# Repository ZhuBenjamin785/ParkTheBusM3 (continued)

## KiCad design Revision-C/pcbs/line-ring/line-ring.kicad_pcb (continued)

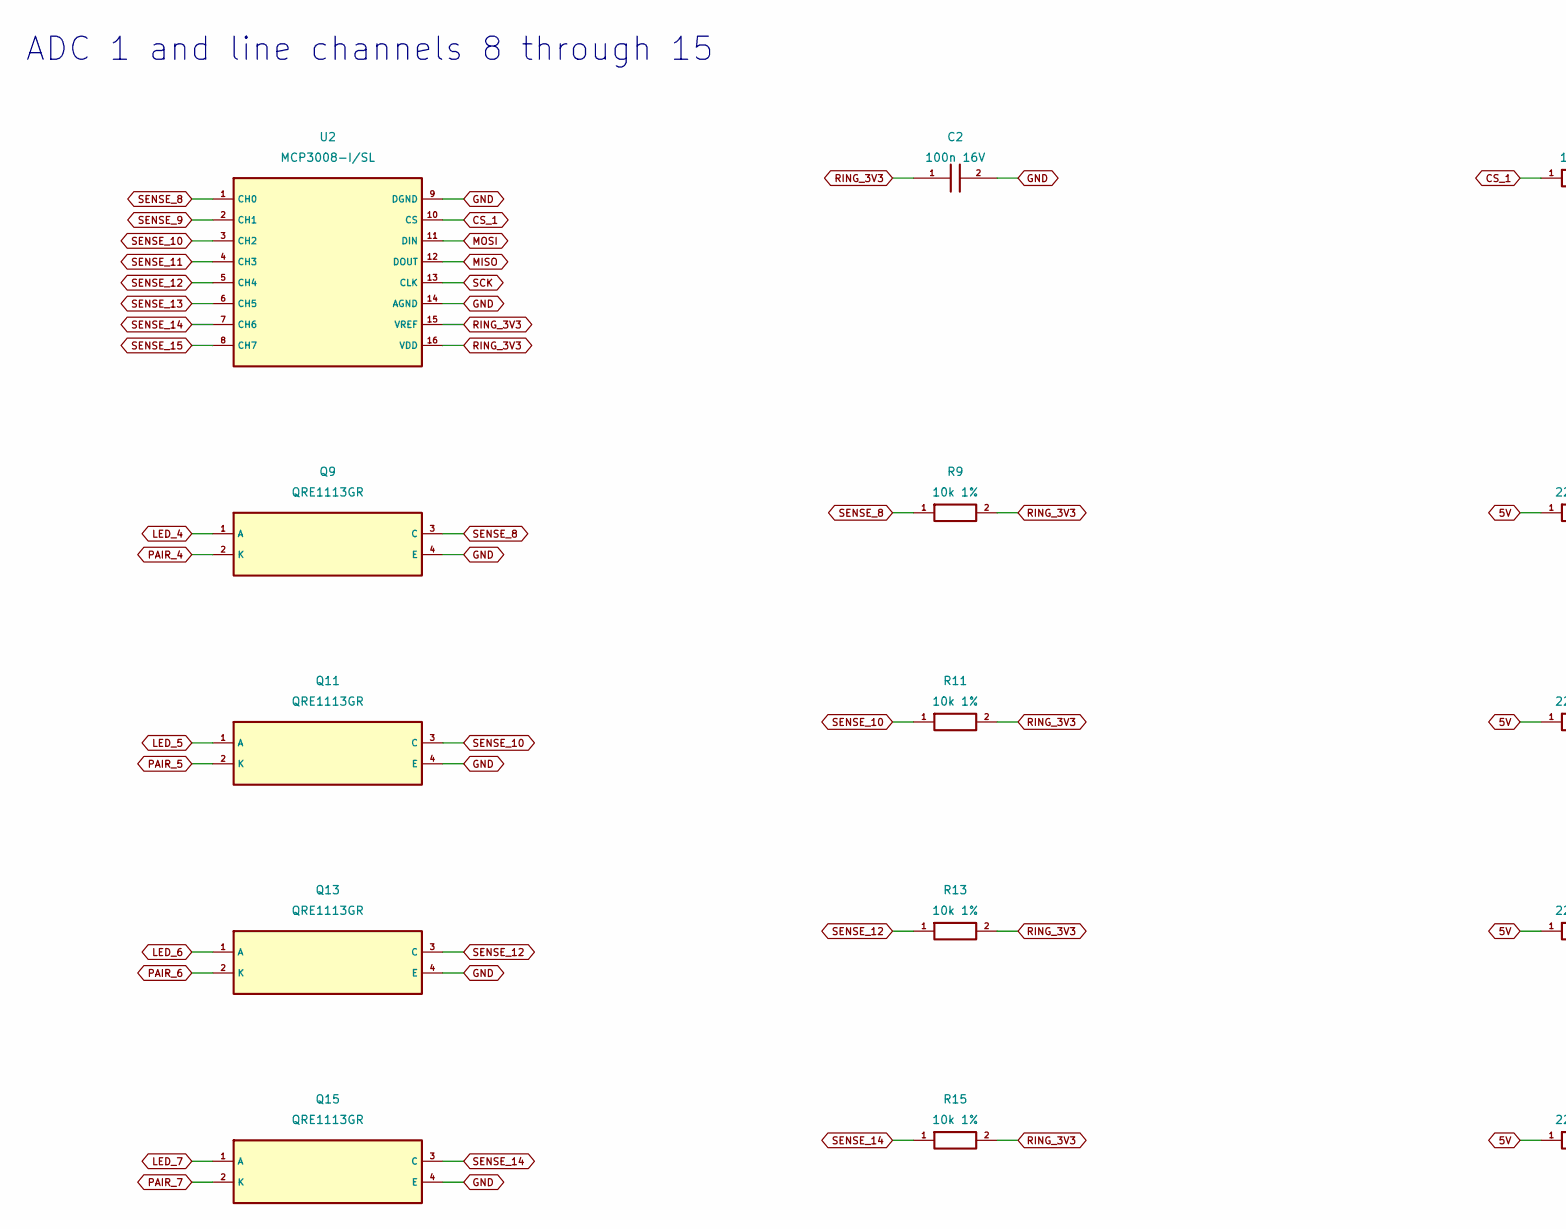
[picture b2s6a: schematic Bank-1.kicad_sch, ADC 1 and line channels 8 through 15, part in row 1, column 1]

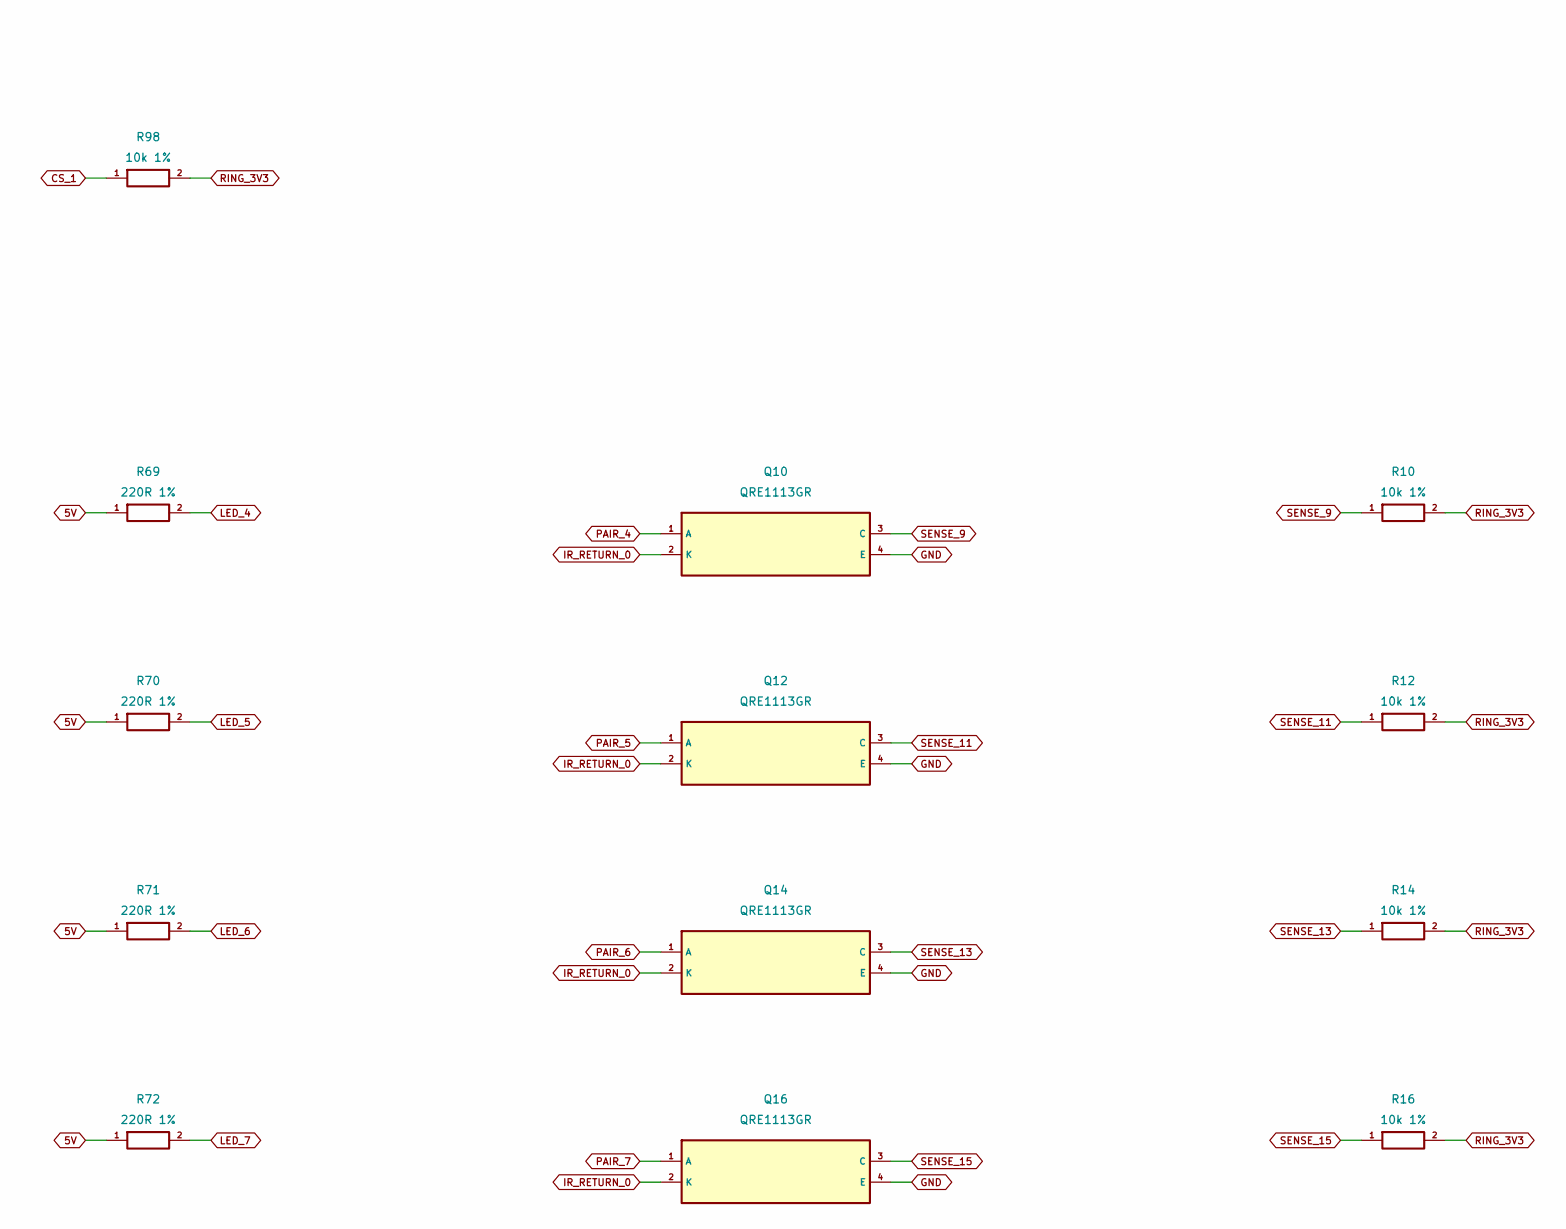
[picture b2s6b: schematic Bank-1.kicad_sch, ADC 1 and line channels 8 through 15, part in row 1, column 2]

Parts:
C2: 100n 16V; C_0805_2012Metric
Q9, Q10, Q11, Q12, Q13, Q14, Q15, Q16: QRE1113GR; OnSemi_CASE100CY
R9, R10, R11, R12, R13, R14, R15, R16, R98: 10k 1%; R_0805_2012Metric
R69, R70, R71, R72: 220R 1%; R_0805_2012Metric
U2: MCP3008-I/SL; SOIC-16_3.9x9.9mm_P1.27mm

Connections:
5V: R69.1, R70.1, R71.1, R72.1; also elsewhere on the board
CS_1: R98.1, U2.10 (CS); also elsewhere on the board
GND: C2.2, Q9.4 (E), Q10.4 (E), Q11.4 (E), Q12.4 (E), Q13.4 (E), Q14.4 (E), Q15.4 (E), Q16.4 (E), U2.9 (DGND), U2.14 (AGND); also elsewhere on the board
IR_RETURN_0: Q10.2 (K), Q12.2 (K), Q14.2 (K), Q16.2 (K); also elsewhere on the board
LED_4: Q9.1 (A), R69.2
LED_5: Q11.1 (A), R70.2
LED_6: Q13.1 (A), R71.2
LED_7: Q15.1 (A), R72.2
MISO: U2.12 (DOUT); also elsewhere on the board
MOSI: U2.11 (DIN); also elsewhere on the board
PAIR_4: Q9.2 (K), Q10.1 (A)
PAIR_5: Q11.2 (K), Q12.1 (A)
PAIR_6: Q13.2 (K), Q14.1 (A)
PAIR_7: Q15.2 (K), Q16.1 (A)
RING_3V3: C2.1, R9.2, R10.2, R11.2, R12.2, R13.2, R14.2, R15.2, R16.2, R98.2, U2.15 (VREF), U2.16 (VDD); also elsewhere on the board
SCK: U2.13 (CLK); also elsewhere on the board
SENSE_8: Q9.3 (C), R9.1, U2.1 (CH0)
SENSE_9: Q10.3 (C), R10.1, U2.2 (CH1)
SENSE_10: Q11.3 (C), R11.1, U2.3 (CH2)
SENSE_11: Q12.3 (C), R12.1, U2.4 (CH3)
SENSE_12: Q13.3 (C), R13.1, U2.5 (CH4)
SENSE_13: Q14.3 (C), R14.1, U2.6 (CH5)
SENSE_14: Q15.3 (C), R15.1, U2.7 (CH6)
SENSE_15: Q16.3 (C), R16.1, U2.8 (CH7)

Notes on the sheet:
ADC 1 and line channels 8 through 15

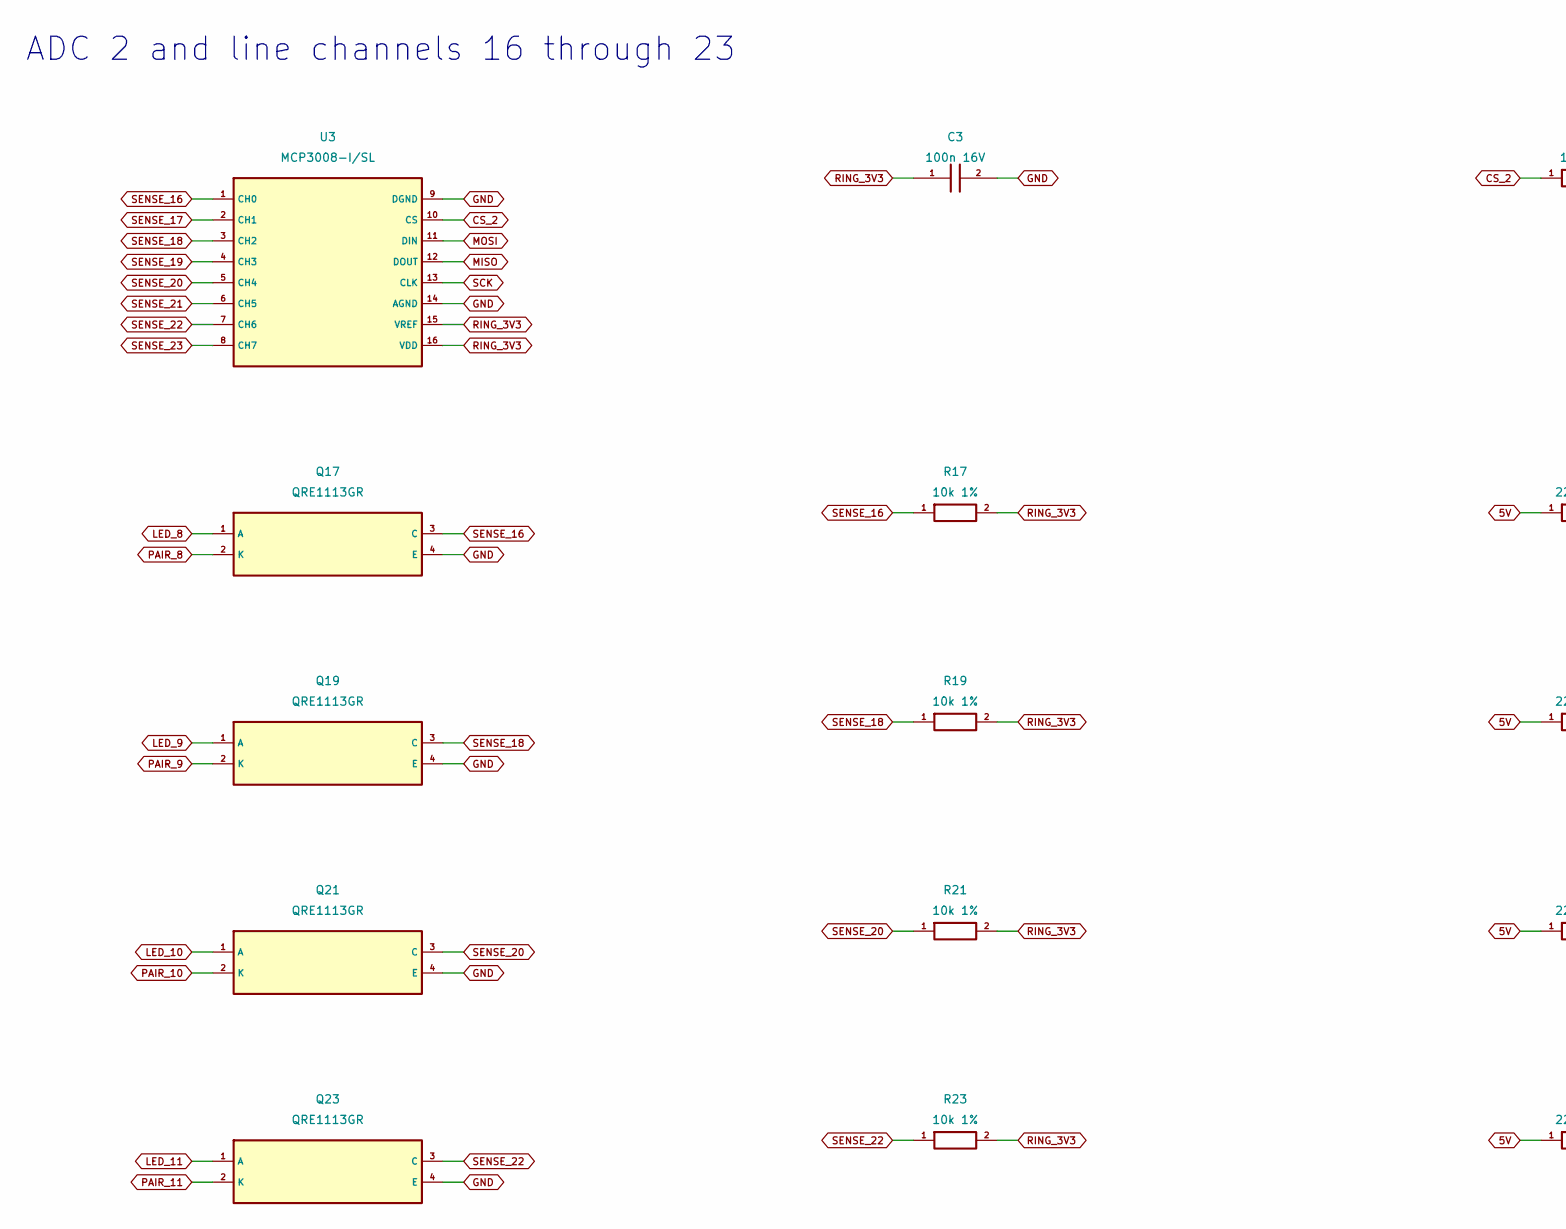
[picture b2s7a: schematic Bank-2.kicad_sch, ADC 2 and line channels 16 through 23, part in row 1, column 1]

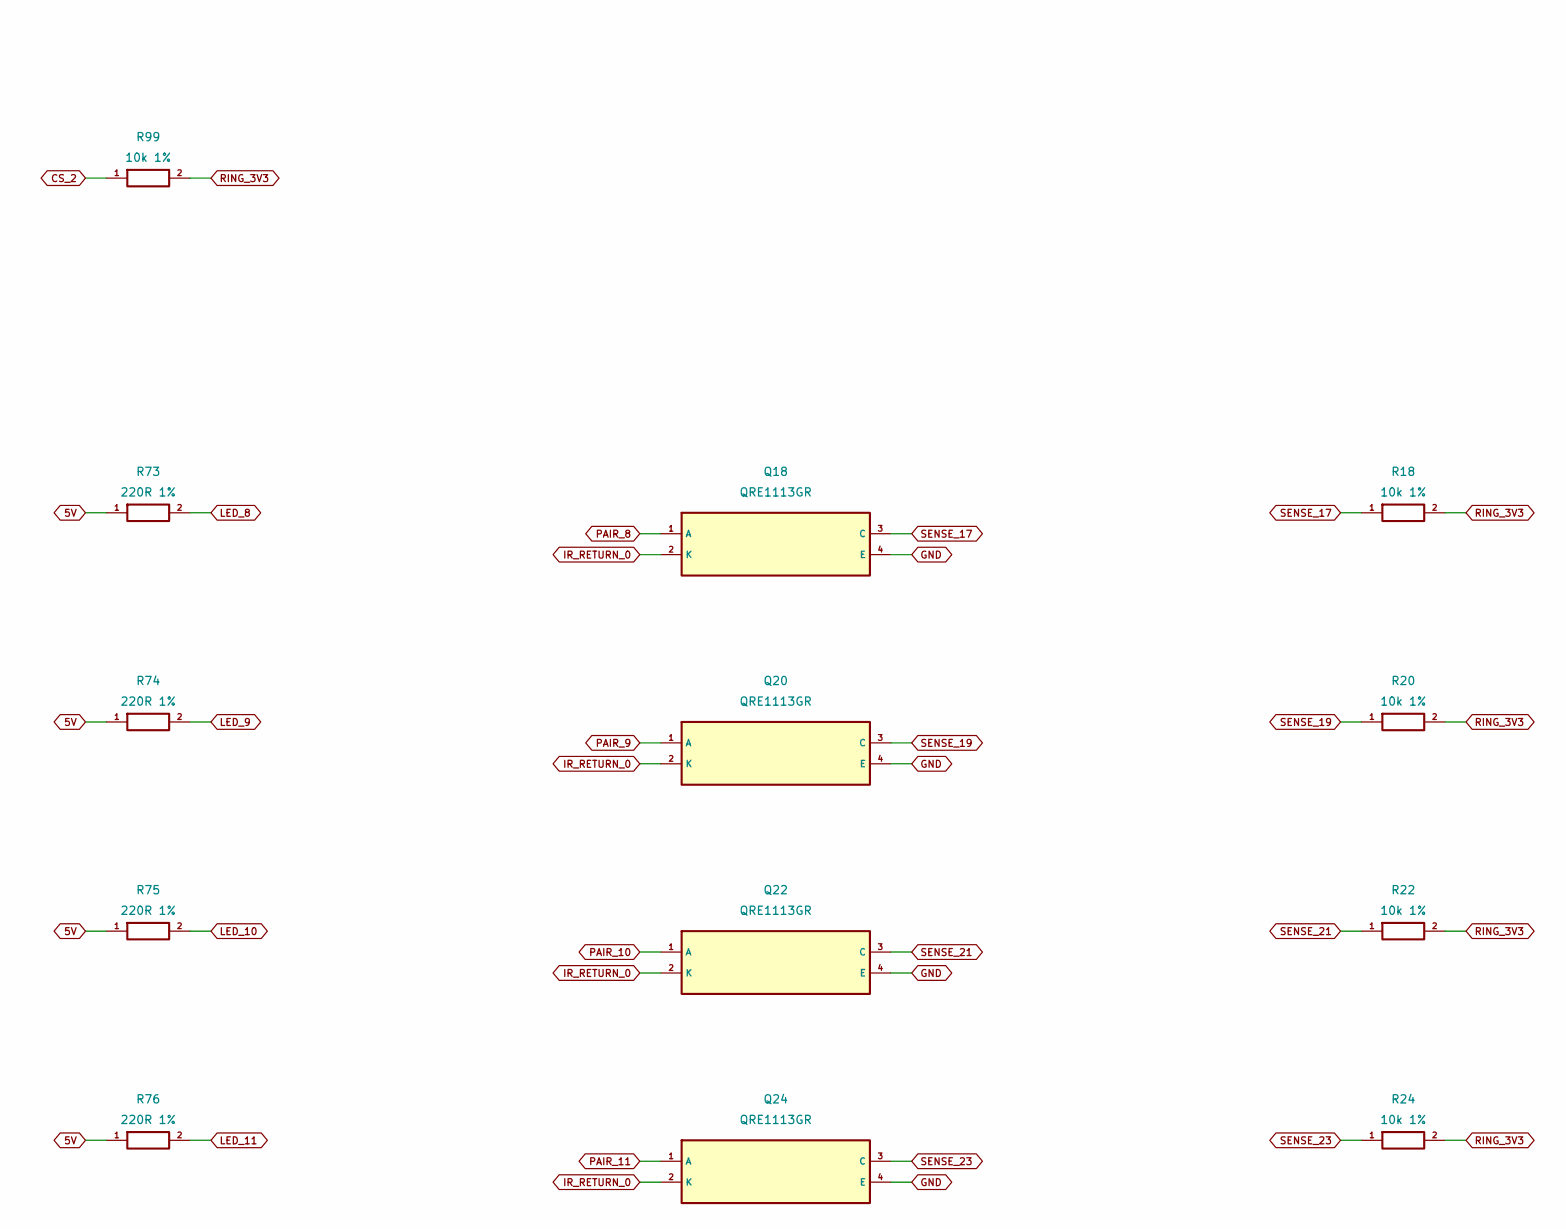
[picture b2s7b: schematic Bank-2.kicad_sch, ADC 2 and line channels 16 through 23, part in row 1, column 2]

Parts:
C3: 100n 16V; C_0805_2012Metric
Q17, Q18, Q19, Q20, Q21, Q22, Q23, Q24: QRE1113GR; OnSemi_CASE100CY
R17, R18, R19, R20, R21, R22, R23, R24, R99: 10k 1%; R_0805_2012Metric
R73, R74, R75, R76: 220R 1%; R_0805_2012Metric
U3: MCP3008-I/SL; SOIC-16_3.9x9.9mm_P1.27mm

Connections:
5V: R73.1, R74.1, R75.1, R76.1; also elsewhere on the board
CS_2: R99.1, U3.10 (CS); also elsewhere on the board
GND: C3.2, Q17.4 (E), Q18.4 (E), Q19.4 (E), Q20.4 (E), Q21.4 (E), Q22.4 (E), Q23.4 (E), Q24.4 (E), U3.9 (DGND), U3.14 (AGND); also elsewhere on the board
IR_RETURN_0: Q18.2 (K), Q20.2 (K), Q22.2 (K), Q24.2 (K); also elsewhere on the board
LED_8: Q17.1 (A), R73.2
LED_9: Q19.1 (A), R74.2
LED_10: Q21.1 (A), R75.2
LED_11: Q23.1 (A), R76.2
MISO: U3.12 (DOUT); also elsewhere on the board
MOSI: U3.11 (DIN); also elsewhere on the board
PAIR_8: Q17.2 (K), Q18.1 (A)
PAIR_9: Q19.2 (K), Q20.1 (A)
PAIR_10: Q21.2 (K), Q22.1 (A)
PAIR_11: Q23.2 (K), Q24.1 (A)
RING_3V3: C3.1, R17.2, R18.2, R19.2, R20.2, R21.2, R22.2, R23.2, R24.2, R99.2, U3.15 (VREF), U3.16 (VDD); also elsewhere on the board
SCK: U3.13 (CLK); also elsewhere on the board
SENSE_16: Q17.3 (C), R17.1, U3.1 (CH0)
SENSE_17: Q18.3 (C), R18.1, U3.2 (CH1)
SENSE_18: Q19.3 (C), R19.1, U3.3 (CH2)
SENSE_19: Q20.3 (C), R20.1, U3.4 (CH3)
SENSE_20: Q21.3 (C), R21.1, U3.5 (CH4)
SENSE_21: Q22.3 (C), R22.1, U3.6 (CH5)
SENSE_22: Q23.3 (C), R23.1, U3.7 (CH6)
SENSE_23: Q24.3 (C), R24.1, U3.8 (CH7)

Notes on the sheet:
ADC 2 and line channels 16 through 23

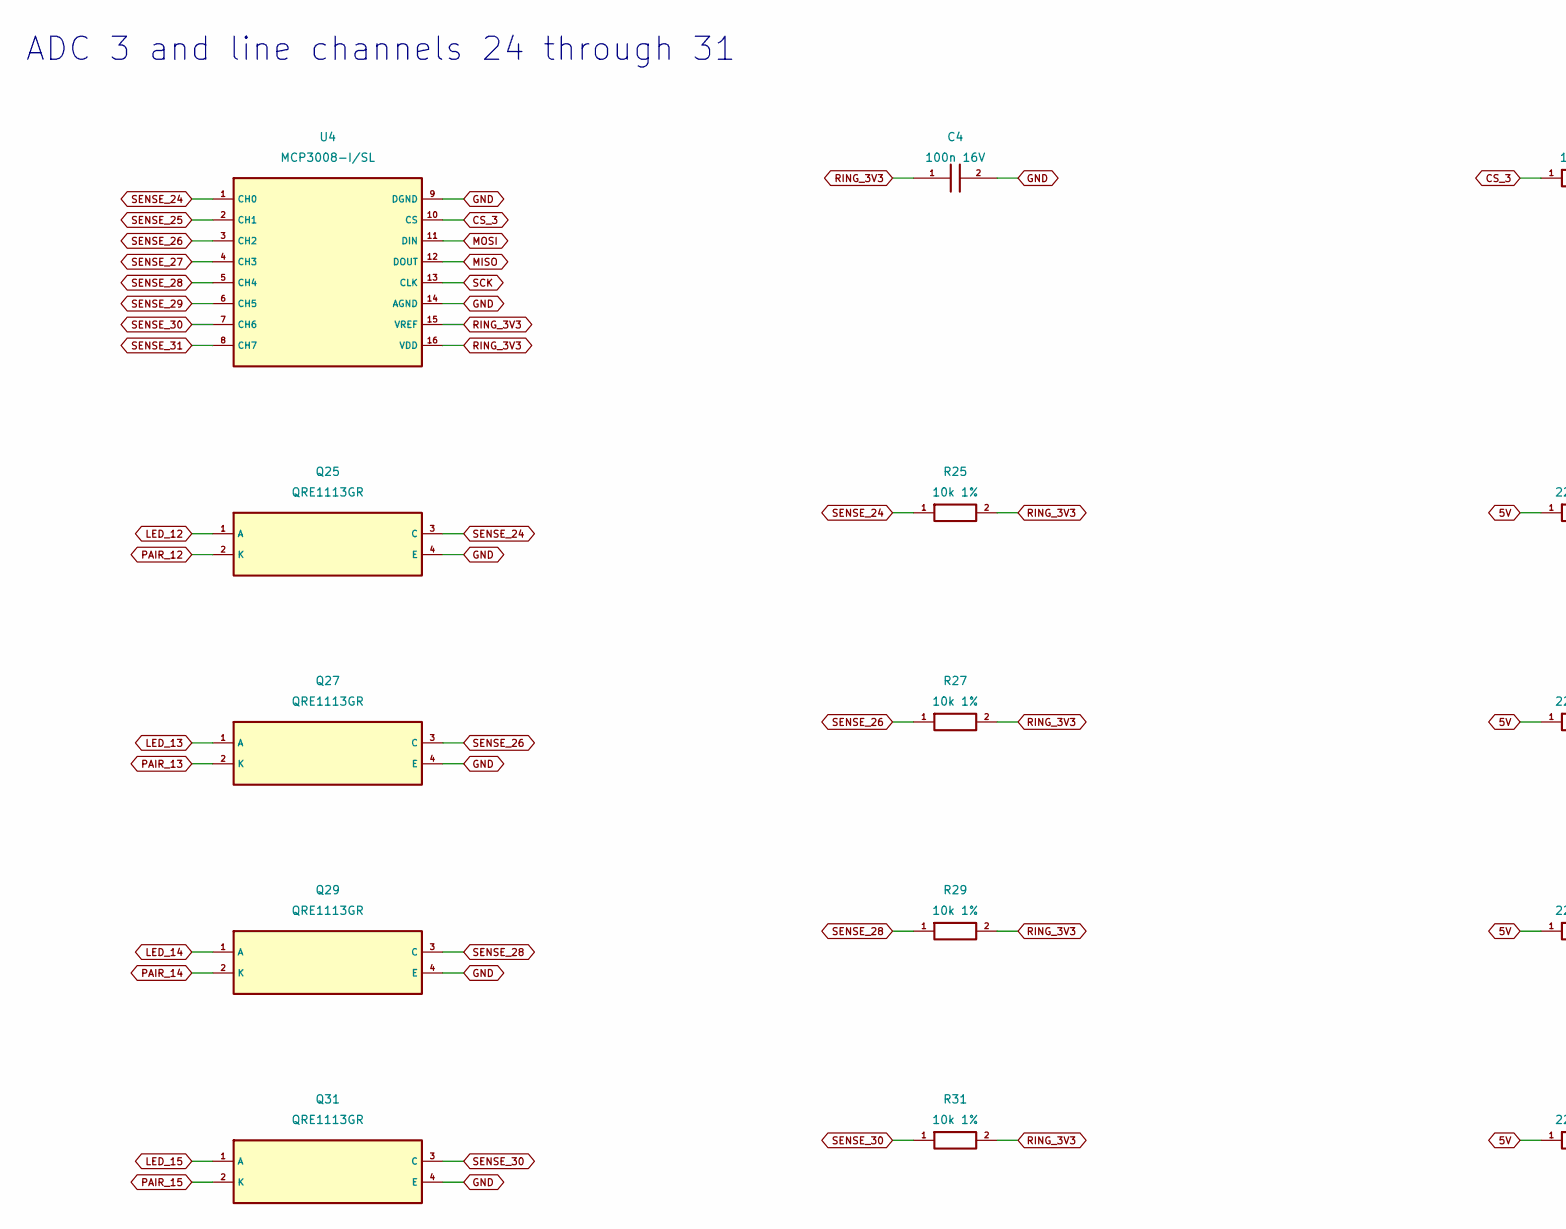
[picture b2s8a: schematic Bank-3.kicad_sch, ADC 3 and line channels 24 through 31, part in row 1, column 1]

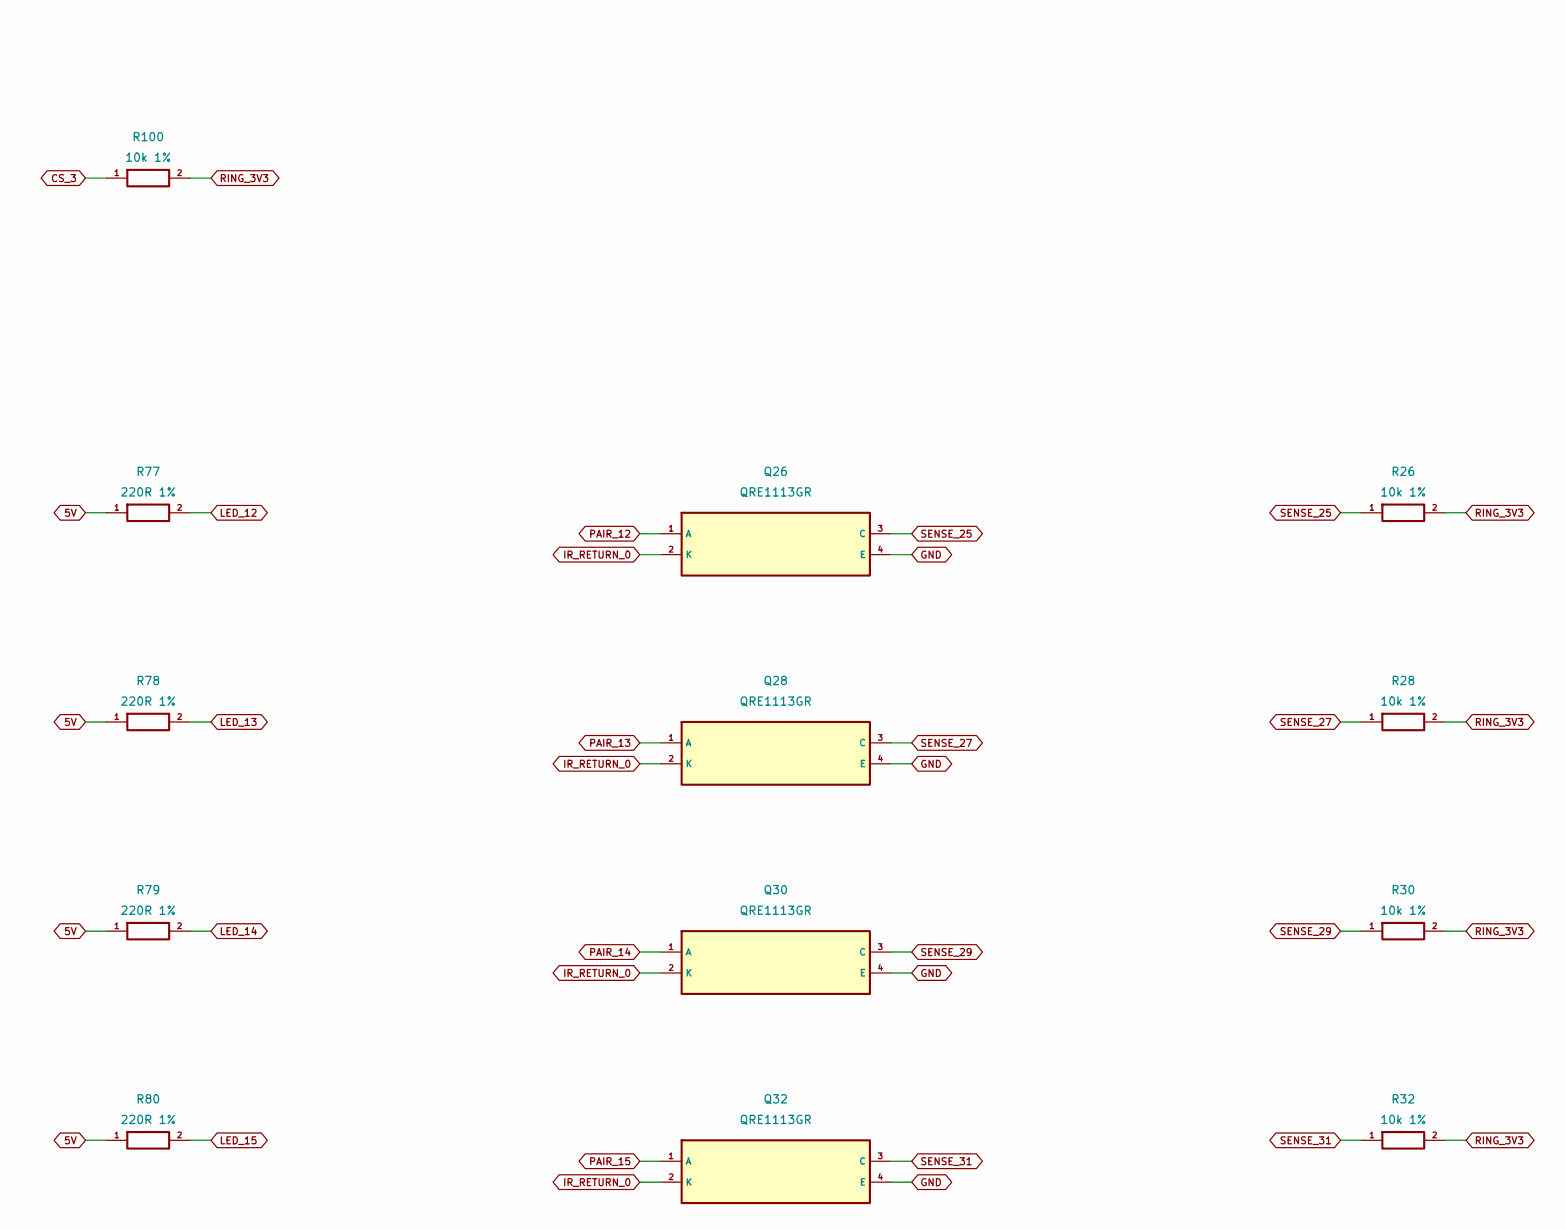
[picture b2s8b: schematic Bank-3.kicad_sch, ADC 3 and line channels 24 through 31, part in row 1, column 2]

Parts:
C4: 100n 16V; C_0805_2012Metric
Q25, Q26, Q27, Q28, Q29, Q30, Q31, Q32: QRE1113GR; OnSemi_CASE100CY
R25, R26, R27, R28, R29, R30, R31, R32, R100: 10k 1%; R_0805_2012Metric
R77, R78, R79, R80: 220R 1%; R_0805_2012Metric
U4: MCP3008-I/SL; SOIC-16_3.9x9.9mm_P1.27mm

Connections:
5V: R77.1, R78.1, R79.1, R80.1; also elsewhere on the board
CS_3: R100.1, U4.10 (CS); also elsewhere on the board
GND: C4.2, Q25.4 (E), Q26.4 (E), Q27.4 (E), Q28.4 (E), Q29.4 (E), Q30.4 (E), Q31.4 (E), Q32.4 (E), U4.9 (DGND), U4.14 (AGND); also elsewhere on the board
IR_RETURN_0: Q26.2 (K), Q28.2 (K), Q30.2 (K), Q32.2 (K); also elsewhere on the board
LED_12: Q25.1 (A), R77.2
LED_13: Q27.1 (A), R78.2
LED_14: Q29.1 (A), R79.2
LED_15: Q31.1 (A), R80.2
MISO: U4.12 (DOUT); also elsewhere on the board
MOSI: U4.11 (DIN); also elsewhere on the board
PAIR_12: Q25.2 (K), Q26.1 (A)
PAIR_13: Q27.2 (K), Q28.1 (A)
PAIR_14: Q29.2 (K), Q30.1 (A)
PAIR_15: Q31.2 (K), Q32.1 (A)
RING_3V3: C4.1, R25.2, R26.2, R27.2, R28.2, R29.2, R30.2, R31.2, R32.2, R100.2, U4.15 (VREF), U4.16 (VDD); also elsewhere on the board
SCK: U4.13 (CLK); also elsewhere on the board
SENSE_24: Q25.3 (C), R25.1, U4.1 (CH0)
SENSE_25: Q26.3 (C), R26.1, U4.2 (CH1)
SENSE_26: Q27.3 (C), R27.1, U4.3 (CH2)
SENSE_27: Q28.3 (C), R28.1, U4.4 (CH3)
SENSE_28: Q29.3 (C), R29.1, U4.5 (CH4)
SENSE_29: Q30.3 (C), R30.1, U4.6 (CH5)
SENSE_30: Q31.3 (C), R31.1, U4.7 (CH6)
SENSE_31: Q32.3 (C), R32.1, U4.8 (CH7)

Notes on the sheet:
ADC 3 and line channels 24 through 31

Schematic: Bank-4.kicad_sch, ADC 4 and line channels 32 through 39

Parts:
C5: 100n 16V; C_0805_2012Metric
Q33, Q34, Q35, Q36, Q37, Q38, Q39, Q40: QRE1113GR; OnSemi_CASE100CY
R33, R34, R35, R36, R37, R38, R39, R40, R101: 10k 1%; R_0805_2012Metric
R81, R82, R83, R84: 220R 1%; R_0805_2012Metric
U5: MCP3008-I/SL; SOIC-16_3.9x9.9mm_P1.27mm

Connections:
5V: R81.1, R82.1, R83.1, R84.1; also elsewhere on the board
CS_4: R101.1, U5.10 (CS); also elsewhere on the board
GND: C5.2, Q33.4 (E), Q34.4 (E), Q35.4 (E), Q36.4 (E), Q37.4 (E), Q38.4 (E), Q39.4 (E), Q40.4 (E), U5.9 (DGND), U5.14 (AGND); also elsewhere on the board
IR_RETURN_1: Q34.2 (K), Q36.2 (K), Q38.2 (K), Q40.2 (K); also elsewhere on the board
LED_16: Q33.1 (A), R81.2
LED_17: Q35.1 (A), R82.2
LED_18: Q37.1 (A), R83.2
LED_19: Q39.1 (A), R84.2
MISO: U5.12 (DOUT); also elsewhere on the board
MOSI: U5.11 (DIN); also elsewhere on the board
PAIR_16: Q33.2 (K), Q34.1 (A)
PAIR_17: Q35.2 (K), Q36.1 (A)
PAIR_18: Q37.2 (K), Q38.1 (A)
PAIR_19: Q39.2 (K), Q40.1 (A)
RING_3V3: C5.1, R33.2, R34.2, R35.2, R36.2, R37.2, R38.2, R39.2, R40.2, R101.2, U5.15 (VREF), U5.16 (VDD); also elsewhere on the board
SCK: U5.13 (CLK); also elsewhere on the board
SENSE_32: Q33.3 (C), R33.1, U5.1 (CH0)
SENSE_33: Q34.3 (C), R34.1, U5.2 (CH1)
SENSE_34: Q35.3 (C), R35.1, U5.3 (CH2)
SENSE_35: Q36.3 (C), R36.1, U5.4 (CH3)
SENSE_36: Q37.3 (C), R37.1, U5.5 (CH4)
SENSE_37: Q38.3 (C), R38.1, U5.6 (CH5)
SENSE_38: Q39.3 (C), R39.1, U5.7 (CH6)
SENSE_39: Q40.3 (C), R40.1, U5.8 (CH7)

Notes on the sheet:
ADC 4 and line channels 32 through 39

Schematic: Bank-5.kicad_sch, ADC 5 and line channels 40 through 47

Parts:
C6: 100n 16V; C_0805_2012Metric
Q41, Q42, Q43, Q44, Q45, Q46, Q47, Q48: QRE1113GR; OnSemi_CASE100CY
R41, R42, R43, R44, R45, R46, R47, R48, R102: 10k 1%; R_0805_2012Metric
R85, R86, R87, R88: 220R 1%; R_0805_2012Metric
U6: MCP3008-I/SL; SOIC-16_3.9x9.9mm_P1.27mm

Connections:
5V: R85.1, R86.1, R87.1, R88.1; also elsewhere on the board
CS_5: R102.1, U6.10 (CS); also elsewhere on the board
GND: C6.2, Q41.4 (E), Q42.4 (E), Q43.4 (E), Q44.4 (E), Q45.4 (E), Q46.4 (E), Q47.4 (E), Q48.4 (E), U6.9 (DGND), U6.14 (AGND); also elsewhere on the board
IR_RETURN_1: Q42.2 (K), Q44.2 (K), Q46.2 (K), Q48.2 (K); also elsewhere on the board
LED_20: Q41.1 (A), R85.2
LED_21: Q43.1 (A), R86.2
LED_22: Q45.1 (A), R87.2
LED_23: Q47.1 (A), R88.2
MISO: U6.12 (DOUT); also elsewhere on the board
MOSI: U6.11 (DIN); also elsewhere on the board
PAIR_20: Q41.2 (K), Q42.1 (A)
PAIR_21: Q43.2 (K), Q44.1 (A)
PAIR_22: Q45.2 (K), Q46.1 (A)
PAIR_23: Q47.2 (K), Q48.1 (A)
RING_3V3: C6.1, R41.2, R42.2, R43.2, R44.2, R45.2, R46.2, R47.2, R48.2, R102.2, U6.15 (VREF), U6.16 (VDD); also elsewhere on the board
SCK: U6.13 (CLK); also elsewhere on the board
SENSE_40: Q41.3 (C), R41.1, U6.1 (CH0)
SENSE_41: Q42.3 (C), R42.1, U6.2 (CH1)
SENSE_42: Q43.3 (C), R43.1, U6.3 (CH2)
SENSE_43: Q44.3 (C), R44.1, U6.4 (CH3)
SENSE_44: Q45.3 (C), R45.1, U6.5 (CH4)
SENSE_45: Q46.3 (C), R46.1, U6.6 (CH5)
SENSE_46: Q47.3 (C), R47.1, U6.7 (CH6)
SENSE_47: Q48.3 (C), R48.1, U6.8 (CH7)

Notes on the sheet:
ADC 5 and line channels 40 through 47

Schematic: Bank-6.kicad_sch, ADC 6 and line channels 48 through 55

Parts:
C7: 100n 16V; C_0805_2012Metric
Q49, Q50, Q51, Q52, Q53, Q54, Q55, Q56: QRE1113GR; OnSemi_CASE100CY
R49, R50, R51, R52, R53, R54, R55, R56, R103: 10k 1%; R_0805_2012Metric
R89, R90, R91, R92: 220R 1%; R_0805_2012Metric
U7: MCP3008-I/SL; SOIC-16_3.9x9.9mm_P1.27mm

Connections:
5V: R89.1, R90.1, R91.1, R92.1; also elsewhere on the board
CS_6: R103.1, U7.10 (CS); also elsewhere on the board
GND: C7.2, Q49.4 (E), Q50.4 (E), Q51.4 (E), Q52.4 (E), Q53.4 (E), Q54.4 (E), Q55.4 (E), Q56.4 (E), U7.9 (DGND), U7.14 (AGND); also elsewhere on the board
IR_RETURN_1: Q50.2 (K), Q52.2 (K), Q54.2 (K), Q56.2 (K); also elsewhere on the board
LED_24: Q49.1 (A), R89.2
LED_25: Q51.1 (A), R90.2
LED_26: Q53.1 (A), R91.2
LED_27: Q55.1 (A), R92.2
MISO: U7.12 (DOUT); also elsewhere on the board
MOSI: U7.11 (DIN); also elsewhere on the board
PAIR_24: Q49.2 (K), Q50.1 (A)
PAIR_25: Q51.2 (K), Q52.1 (A)
PAIR_26: Q53.2 (K), Q54.1 (A)
PAIR_27: Q55.2 (K), Q56.1 (A)
RING_3V3: C7.1, R49.2, R50.2, R51.2, R52.2, R53.2, R54.2, R55.2, R56.2, R103.2, U7.15 (VREF), U7.16 (VDD); also elsewhere on the board
SCK: U7.13 (CLK); also elsewhere on the board
SENSE_48: Q49.3 (C), R49.1, U7.1 (CH0)
SENSE_49: Q50.3 (C), R50.1, U7.2 (CH1)
SENSE_50: Q51.3 (C), R51.1, U7.3 (CH2)
SENSE_51: Q52.3 (C), R52.1, U7.4 (CH3)
SENSE_52: Q53.3 (C), R53.1, U7.5 (CH4)
SENSE_53: Q54.3 (C), R54.1, U7.6 (CH5)
SENSE_54: Q55.3 (C), R55.1, U7.7 (CH6)
SENSE_55: Q56.3 (C), R56.1, U7.8 (CH7)

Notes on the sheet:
ADC 6 and line channels 48 through 55

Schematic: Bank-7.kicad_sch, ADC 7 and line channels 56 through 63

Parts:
C8: 100n 16V; C_0805_2012Metric
Q57, Q58, Q59, Q60, Q61, Q62, Q63, Q64: QRE1113GR; OnSemi_CASE100CY
R57, R58, R59, R60, R61, R62, R63, R64, R104: 10k 1%; R_0805_2012Metric
R93, R94, R95, R96: 220R 1%; R_0805_2012Metric
U8: MCP3008-I/SL; SOIC-16_3.9x9.9mm_P1.27mm

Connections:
5V: R93.1, R94.1, R95.1, R96.1; also elsewhere on the board
CS_7: R104.1, U8.10 (CS); also elsewhere on the board
GND: C8.2, Q57.4 (E), Q58.4 (E), Q59.4 (E), Q60.4 (E), Q61.4 (E), Q62.4 (E), Q63.4 (E), Q64.4 (E), U8.9 (DGND), U8.14 (AGND); also elsewhere on the board
IR_RETURN_1: Q58.2 (K), Q60.2 (K), Q62.2 (K), Q64.2 (K); also elsewhere on the board
LED_28: Q57.1 (A), R93.2
LED_29: Q59.1 (A), R94.2
LED_30: Q61.1 (A), R95.2
LED_31: Q63.1 (A), R96.2
MISO: U8.12 (DOUT); also elsewhere on the board
MOSI: U8.11 (DIN); also elsewhere on the board
PAIR_28: Q57.2 (K), Q58.1 (A)
PAIR_29: Q59.2 (K), Q60.1 (A)
PAIR_30: Q61.2 (K), Q62.1 (A)
PAIR_31: Q63.2 (K), Q64.1 (A)
RING_3V3: C8.1, R57.2, R58.2, R59.2, R60.2, R61.2, R62.2, R63.2, R64.2, R104.2, U8.15 (VREF), U8.16 (VDD); also elsewhere on the board
SCK: U8.13 (CLK); also elsewhere on the board
SENSE_56: Q57.3 (C), R57.1, U8.1 (CH0)
SENSE_57: Q58.3 (C), R58.1, U8.2 (CH1)
SENSE_58: Q59.3 (C), R59.1, U8.3 (CH2)
SENSE_59: Q60.3 (C), R60.1, U8.4 (CH3)
SENSE_60: Q61.3 (C), R61.1, U8.5 (CH4)
SENSE_61: Q62.3 (C), R62.1, U8.6 (CH5)
SENSE_62: Q63.3 (C), R63.1, U8.7 (CH6)
SENSE_63: Q64.3 (C), R64.1, U8.8 (CH7)

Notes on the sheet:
ADC 7 and line channels 56 through 63

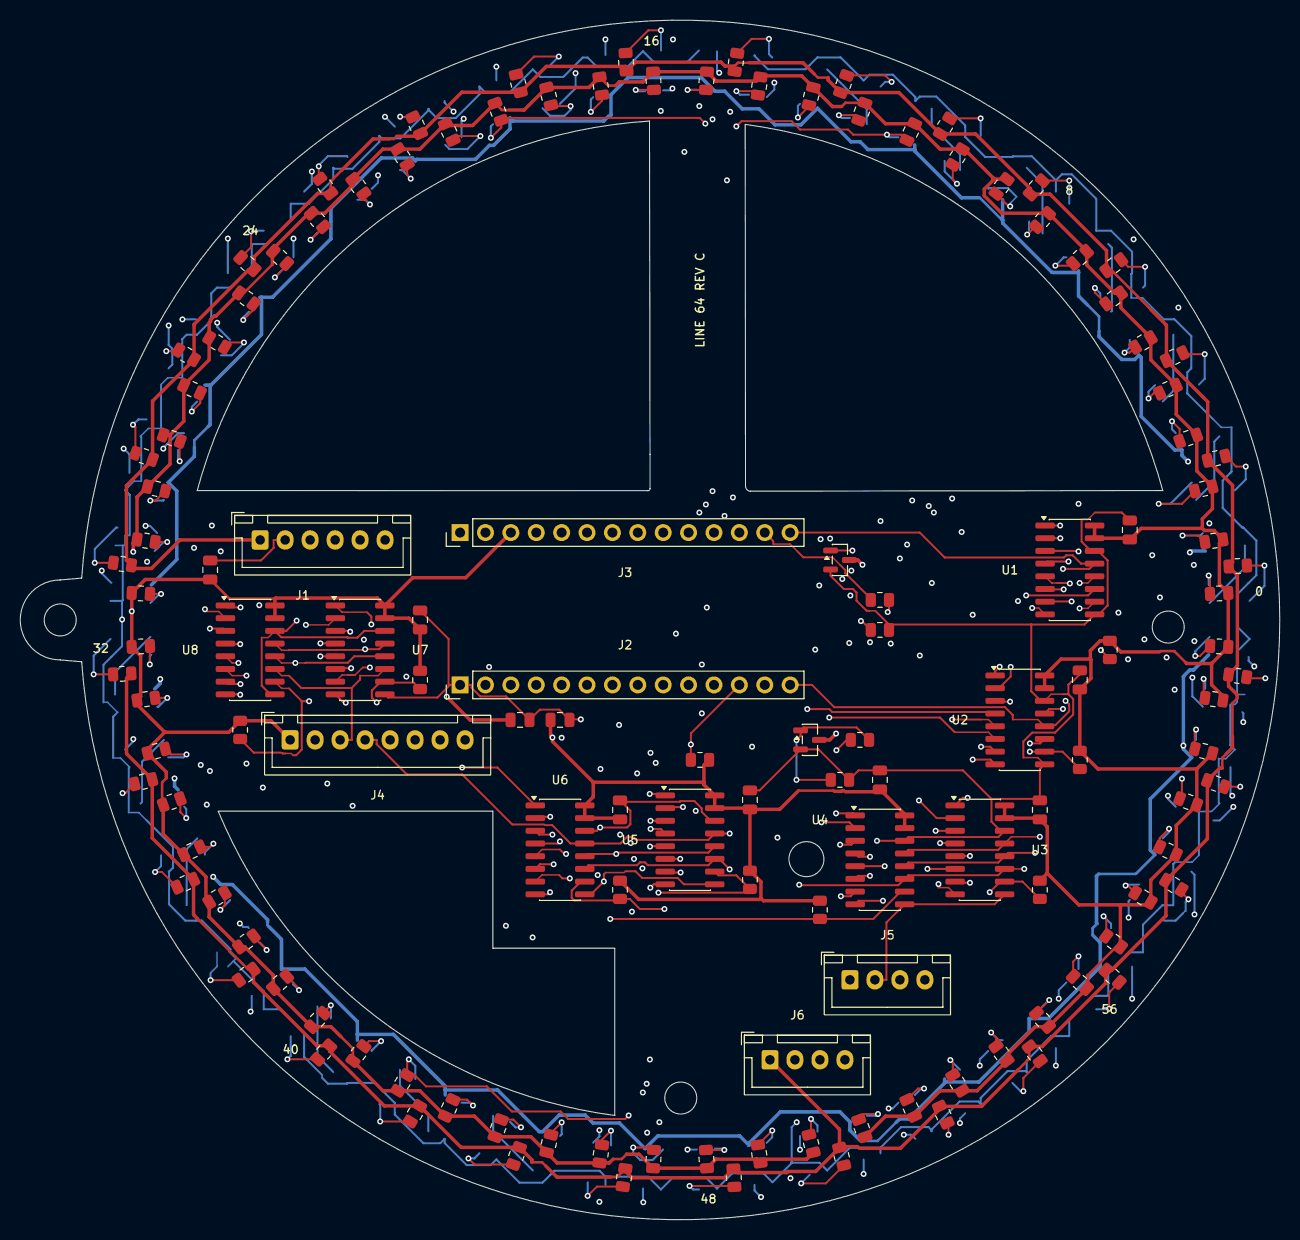
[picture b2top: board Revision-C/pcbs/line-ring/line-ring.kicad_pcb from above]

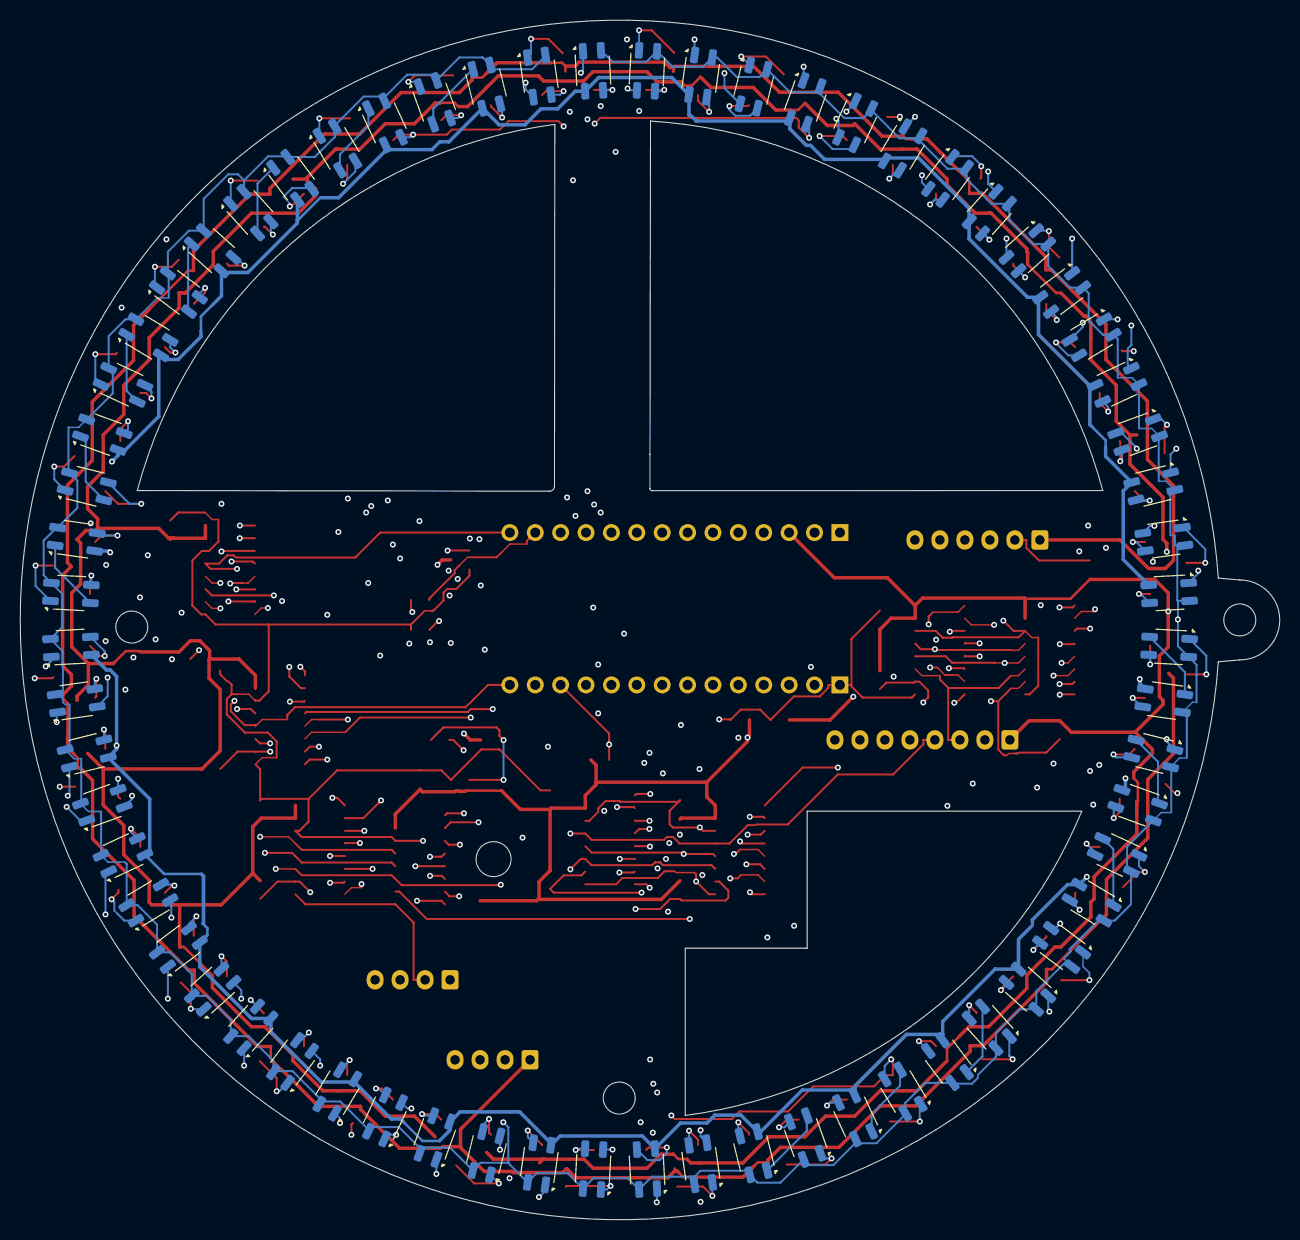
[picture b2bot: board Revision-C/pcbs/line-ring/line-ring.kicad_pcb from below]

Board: 4 copper layers, 126.0 x 120.0 mm, 203 parts (64 on the bottom side), 156 nets.

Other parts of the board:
H1, H2, H3: NPTH 3.2
H4: NPTH 3.5
